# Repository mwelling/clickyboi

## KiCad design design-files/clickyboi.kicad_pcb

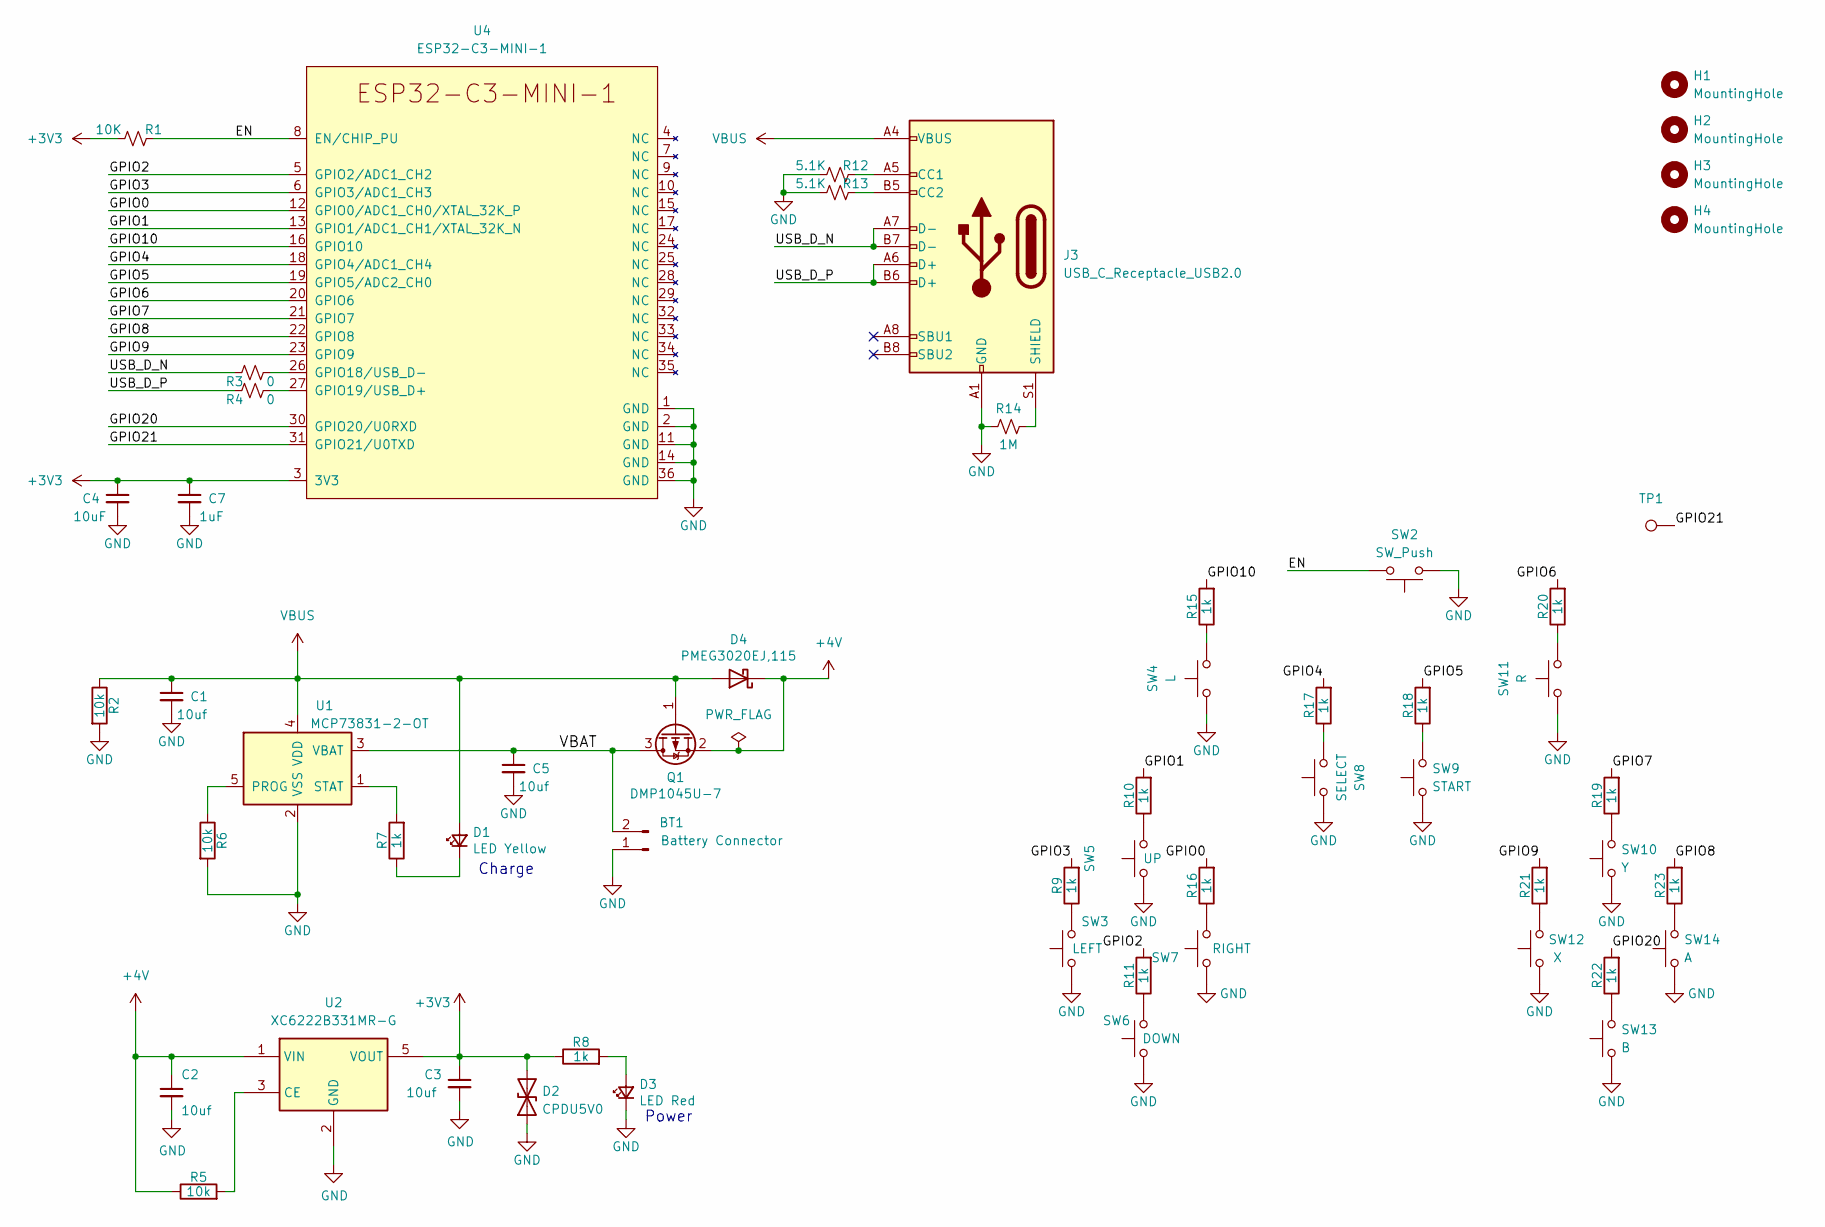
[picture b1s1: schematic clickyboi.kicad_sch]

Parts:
BT1: Battery Connector; JST_PH_B2B-PH-SM4-TB_1x02-1MP_P2.00mm_Vertical
C1, C2, C3, C5: 10uf; C_0805_2012Metric
C4: 10uF; C_0603_1608Metric
C7: 1uF; C_0402_1005Metric
D1: LED Yellow; LED_0603_1608Metric
D2: CPDU5V0; D_0603_1608Metric
D3: LED Red; LED_0603_1608Metric
D4: PMEG3020EJ,115; D_SOD-323F
H1, H2, H3, H4: MountingHole; MountingHole_3.2mm_M3
J3: USB_C_Receptacle_USB2.0; USB_C_Receptacle_HRO_TYPE-C-31-M-12
Q1: DMP1045U-7; SOT-23
R1: 10K; R_0402_1005Metric
R2, R5, R6: 10k; R_0603_1608Metric
R3, R4: 0; R_0402_1005Metric
R7, R8, R9, R10, R11, R15, R16, R17, R18, R19, R20, R21, R22, R23: 1k; R_0603_1608Metric
R12, R13: 5.1K; R_0402_1005Metric
R14: 1M; R_0402_1005Metric
SW2: SW_Push; SW_Push_1P1T-MP_NO_Horizontal_Alps_SKRTLAE010
SW3: LEFT; SW_Push_1P1T_NO_CK_KMR2
SW4: L; SW_Push_1P1T-MP_NO_Horizontal_Alps_SKRTLAE010
SW5: UP; SW_Push_1P1T_NO_CK_KMR2
SW6: DOWN; SW_Push_1P1T_NO_CK_KMR2
SW7: RIGHT; SW_Push_1P1T_NO_CK_KMR2
SW8: SELECT; SW_Push_1P1T_NO_CK_KMR2
SW9: START; SW_Push_1P1T_NO_CK_KMR2
SW10: Y; SW_Push_1P1T_NO_CK_KMR2
SW11: R; SW_Push_1P1T-MP_NO_Horizontal_Alps_SKRTLAE010
SW12: X; SW_Push_1P1T_NO_CK_KMR2
SW13: B; SW_Push_1P1T_NO_CK_KMR2
SW14: A; SW_Push_1P1T_NO_CK_KMR2
TP1: TestPoint; TestPoint_Pad_D1.0mm
U1: MCP73831-2-OT; SOT-23-5
U2: XC6222B331MR-G; SOT-23-5
U4: ESP32-C3-MINI-1

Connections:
+3V3: C3.1, C4.1, C7.1, D2.2 (A2), R1.1, R8.1, U2.5 (VOUT), U4.3 (3V3)
+4V: C2.1, D4.1 (K), Q1.2 (S), R5.1, U2.1 (VIN)
/EN: R1.2, SW2.2, U4.8 (EN/CHIP_PU)
/GPIO0: R16.2, U4.12 (GPIO0/ADC1_CH0/XTAL_32K_P)
/GPIO1: R10.2, U4.13 (GPIO1/ADC1_CH1/XTAL_32K_N)
/GPIO2: R11.2, U4.5 (GPIO2/ADC1_CH2)
/GPIO3: R9.2, U4.6 (GPIO3/ADC1_CH3)
/GPIO4: R17.2, U4.18 (GPIO4/ADC1_CH4)
/GPIO5: R18.2, U4.19 (GPIO5/ADC2_CH0)
/GPIO6: R20.2, U4.20 (GPIO6)
/GPIO7: R19.2, U4.21 (GPIO7)
/GPIO8: R23.2, U4.22 (GPIO8)
/GPIO9: R21.2, U4.23 (GPIO9)
/GPIO10: R15.2, U4.16 (GPIO10)
/GPIO20: R22.2, U4.30 (GPIO20/U0RXD)
/GPIO21: TP1.1, U4.31 (GPIO21/U0TXD)
/USB_D_N: J3.A7 (D-), J3.B7 (D-), R3.2
/USB_D_P: J3.A6 (D+), J3.B6 (D+), R4.2
/VBAT: BT1.2, C5.1, Q1.3 (D), U1.3 (VBAT)
GND: BT1.1, C1.2, C2.2, C3.2, C4.2, C5.2, C7.2, D2.1 (A1), D3.1 (K), J3.A1 (GND), J3.A12 (GND), J3.B1 (GND), J3.B12 (GND), R2.2, R6.2, R12.1, R13.1, R14.1, SW2.1, SW3.1, SW4.1, SW5.1, SW6.1, SW7.1, SW8.1, SW9.1, SW10.1, SW11.1, SW12.1, SW13.1, SW14.1, U1.2 (VSS), U2.2 (GND), U4.1 (GND), U4.2 (GND), U4.11 (GND), U4.14 (GND), U4.36 (GND)
unnamed: D1.1 (K), R7.1
unnamed: D3.2 (A), R8.2
unnamed: J3.A5 (CC1), R12.2
unnamed: J3.B5 (CC2), R13.2
unnamed: J3.S1 (SHIELD), R14.2
unnamed: R3.1, U4.26 (GPIO18/USB_D-)
unnamed: R4.1, U4.27 (GPIO19/USB_D+)
unnamed: R5.2, U2.3 (CE)
unnamed: R6.1, U1.5 (PROG)
unnamed: R7.2, U1.1 (STAT)
unnamed: R9.1, SW3.2
unnamed: R10.1, SW5.2
unnamed: R11.1, SW6.2
unnamed: R15.1, SW4.2
unnamed: R16.1, SW7.2
unnamed: R17.1, SW8.2
unnamed: R18.1, SW9.2
unnamed: R19.1, SW10.2
unnamed: R20.1, SW11.2
unnamed: R21.1, SW12.2
unnamed: R22.1, SW13.2
unnamed: R23.1, SW14.2
VBUS: C1.1, D1.2 (A), D4.2 (A), J3.A4 (VBUS), J3.A9 (VBUS), J3.B4 (VBUS), J3.B9 (VBUS), Q1.1 (G), R2.1, U1.4 (VDD)

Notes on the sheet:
Power
Charge

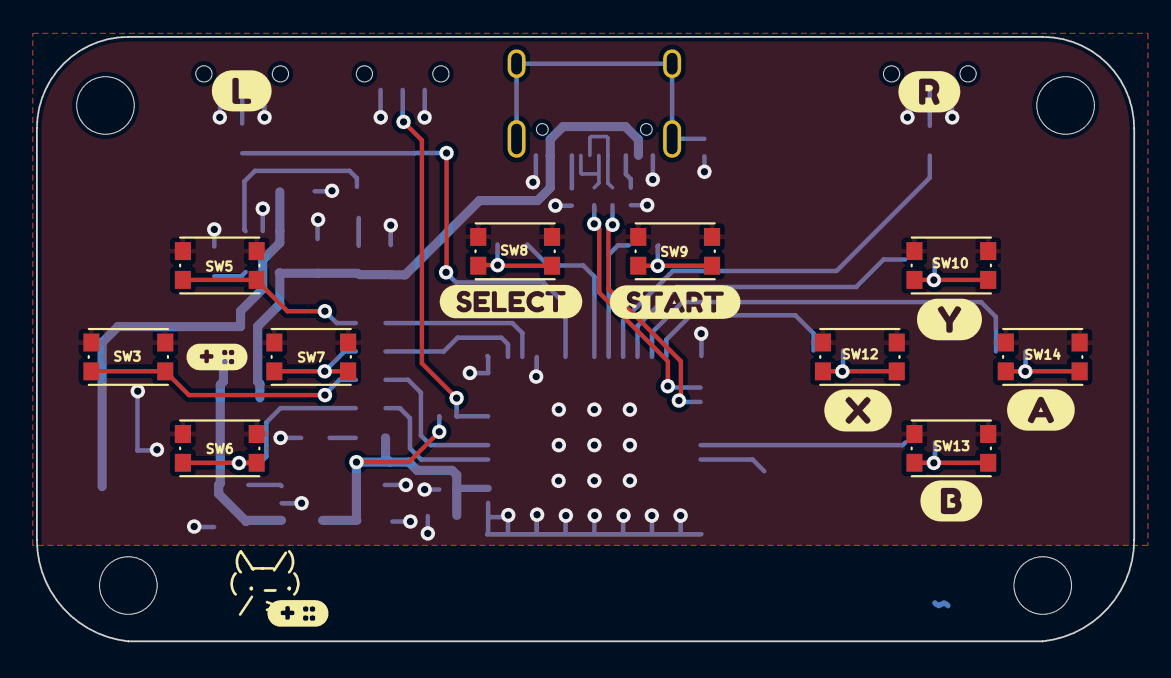
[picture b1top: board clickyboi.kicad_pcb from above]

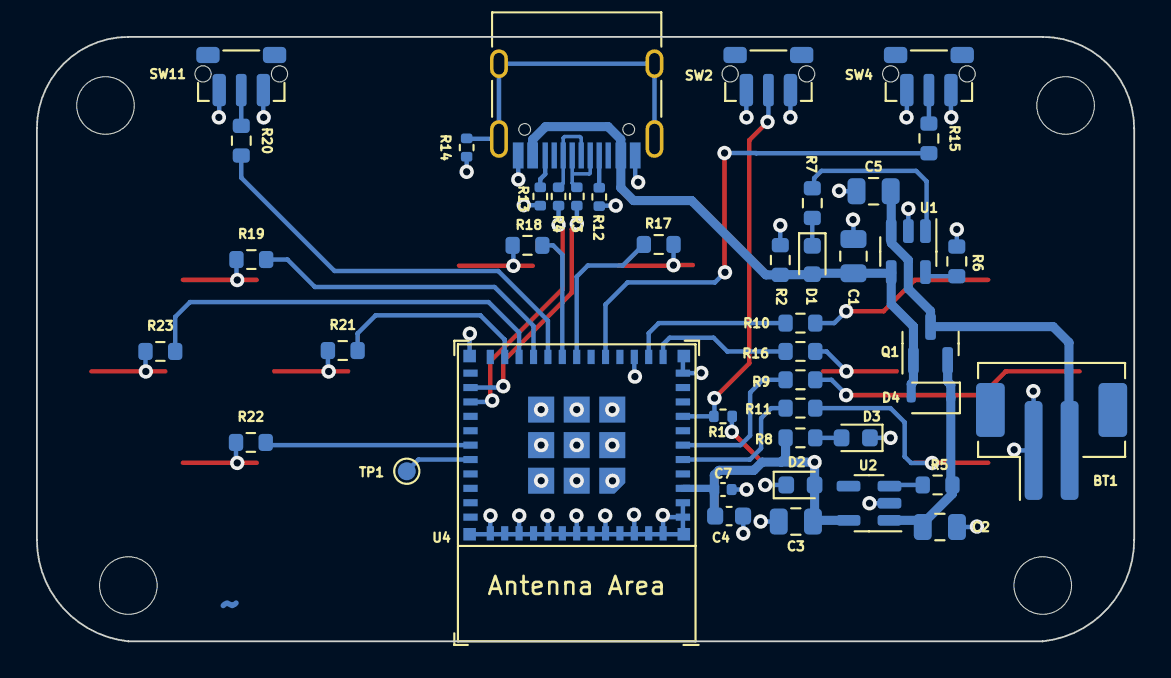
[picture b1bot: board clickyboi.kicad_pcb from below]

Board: 2 copper layers, 61.0 x 33.6 mm, 67 parts (43 on the bottom side), 43 nets.

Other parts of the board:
kibuzzard-63C8BD99, kibuzzard-63C8BD99#2: G***; kibuzzard-63C8BD99
kibuzzard-63C8BFBA: G***; kibuzzard-63C8BFBA
kibuzzard-63C8BFCF: G***; kibuzzard-63C8BFCF
kibuzzard-63C8BFE1: G***; kibuzzard-63C8BFE1
kibuzzard-63C8C00A: G***; kibuzzard-63C8C00A
kibuzzard-63C8C0B2: G***; kibuzzard-63C8C0B2
kibuzzard-63C8C0C1: G***; kibuzzard-63C8C0C1
kibuzzard-63C8C01E: G***; kibuzzard-63C8C01E
kibuzzard-63C8C028: G***; kibuzzard-63C8C028

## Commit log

2025-06-22 Initial commit of clickyboi
2025-06-22 Update README with image and fix library link
